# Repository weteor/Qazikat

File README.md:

### Qazikat

qaz or katana stagger keyboard with offset spacebar, nav cluster and ISO enter

## Features

- flipable pcb, one side supports qaz rowstagger, the other katana stagger
- Hotswap sockets
- onboard rp2040
- indicator leds and underglow 
- production files for pcba
- case file for qaz variant are supplied (stl, dxf, as well as the freecad files)
- QMK with vial support
- completely open source, permissive license ([CERN-OHL-P](https://cern-ohl.web.cern.ch/home))

## Layouts

The pcb support both layouts - not at the same time, you have to choose when soldering hot swap sockets - just flip it around.

## Want one?

All production files you need to build your own board can be found [here](./prod/qazikat). You will also need the usb adapter found [here](./prod/usb)

## Parts

Parts needed for the assembled pcbs:

- 38-41 hotswap sockets
- your favourite switches
- usb adapter board
- 10 pin Type A (contacts on same side) FCC Cable, length about 15cm/6in
- optional: 3 or 21 SK6812MINI E RGB LEDs
- optional: 3 light guides, 2.8mm diameter
- optional: two 3x6mm micro push switches
- optional: for katana a 10pin 0.5mm pitch FCC Connector 

Parts needed for the case:

- 8 M2 heat inserts 

- 8 M2 screws, 8mm length

- 2 M2 screws, 4mm length

- 2 M2 nuts

## Build

- insert heat inserts into the provided holes in the top case. If you used PLA or Nylon, you can just meld them right in. If you have a resin case, check if you the inserts fit, they should go in with just a small amount of force. If that's not the case, try to use a file to widen the hole slightly.

- place the M2 nuts in the hexagonal shaped holes on the bottom and use the 4mm screws to hold the usb adapter board in place

- solder sockets and optionally LEDs (leds are mounted from the backside facing  "through" the pcb).

- If you want to use the underglow pcbs, use some solder to connect both 

- connect fcc cable to usb adaptor and qazikat pcb

## Firmware

firmware configs for qmk(only roughly tested) and vial can be found in [firmware folder](./firmware). Top LED support is still rudimentary and is done in qazikat.c . You can also comment out the functions in that file and also just let the backlight handle those.

The first time the pcb is plugged in, the bootloader will provide a drive to upload the firmware file.

The provided firmware enables to enter bootloader with double tap on the reset button. This can easily be done by shortening the pads with a paperclip or something similar. If this isn't working, try holding down the boot button and while pressed, tip reset.

You may either build the firmware yourself or use the provided vial firmware files [here](./firmware/uf2). You can use VIAL ([download](https://get.vial.today/) to program your board after that, without need to build a new firmware.

## The rest

Everything in this repository is free to use however you might see fit. If you want to support me and my projects, please consider linking back to this repository if you build/change/use anything.

If you would like to send me a tip, you could do it [here](https://ko-fi.com/weteor) (Please don't feel like you have to).

## More pictures

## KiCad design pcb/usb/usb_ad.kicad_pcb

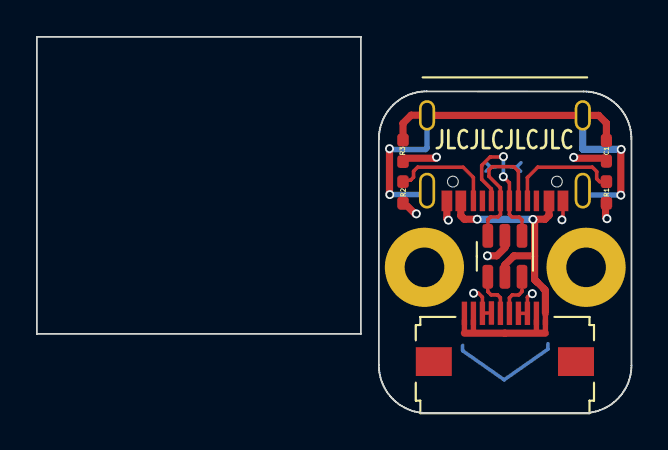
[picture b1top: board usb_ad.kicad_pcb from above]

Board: 2 copper layers, 33.0 x 20.9 mm, 9 parts (0 on the bottom side), 9 nets.

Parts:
C1: 1nF; C_0402_HandSolder
H1, H2: MountingHole_Pad; MountingHole_2.2mm_M2_Pad
J1: USB_C_Receptacle_USB2.0; USB C-31-M-12
J2: Conn_01x10; FCC 1x10 - JUSHUO AFC01-S10FCA-00
R1, R2: 5.1k; R_0402_HandSolder
R3: 1M; R_0402_HandSolder
U1: USBLC6-2SC6; SOT-23-6

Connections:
D+: J2.6, U1.6 (I/O1)
D-: J2.5, U1.4 (I/O2)
Earth: C1.2, J1.S1 (SHIELD), R3.1
GND: C1.1, H1.1, H2.1, J1.A1 (GND), J1.A12 (GND), J1.B1 (GND), J1.B12 (GND), J2.3, J2.4, J2.7, J2.8, R1.2, R2.2, R3.2, U1.2 (GND)
unnamed: J1.A5 (CC1), R1.1
unnamed: J1.B5 (CC2), R2.1
unnamed: J1.A6 (D+), J1.B6 (D+), U1.1 (I/O1)
unnamed: J1.A7 (D-), J1.B7 (D-), U1.3 (I/O2)
VBUS: J1.A4 (VBUS), J1.A9 (VBUS), J1.B4 (VBUS), J1.B9 (VBUS), J2.1, J2.2, J2.9, J2.10, U1.5 (VBUS)

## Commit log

2023-12-08 add pcb data
2023-12-08 add case cad files
2023-12-08 add production files pcb and case
2023-12-08 add images
2023-12-08 add readme and license
2024-01-04 add firmware
2024-01-07 rename image
2024-01-07 readd images
2024-03-27 add case for katana variant
2024-04-10 fix: add missing cutout for stabilizers
2024-04-10 add led support to katana firmware
